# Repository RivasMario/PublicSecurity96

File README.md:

# PublicSecurity96
96% Mechanical Keyboard PCB Kicad Files

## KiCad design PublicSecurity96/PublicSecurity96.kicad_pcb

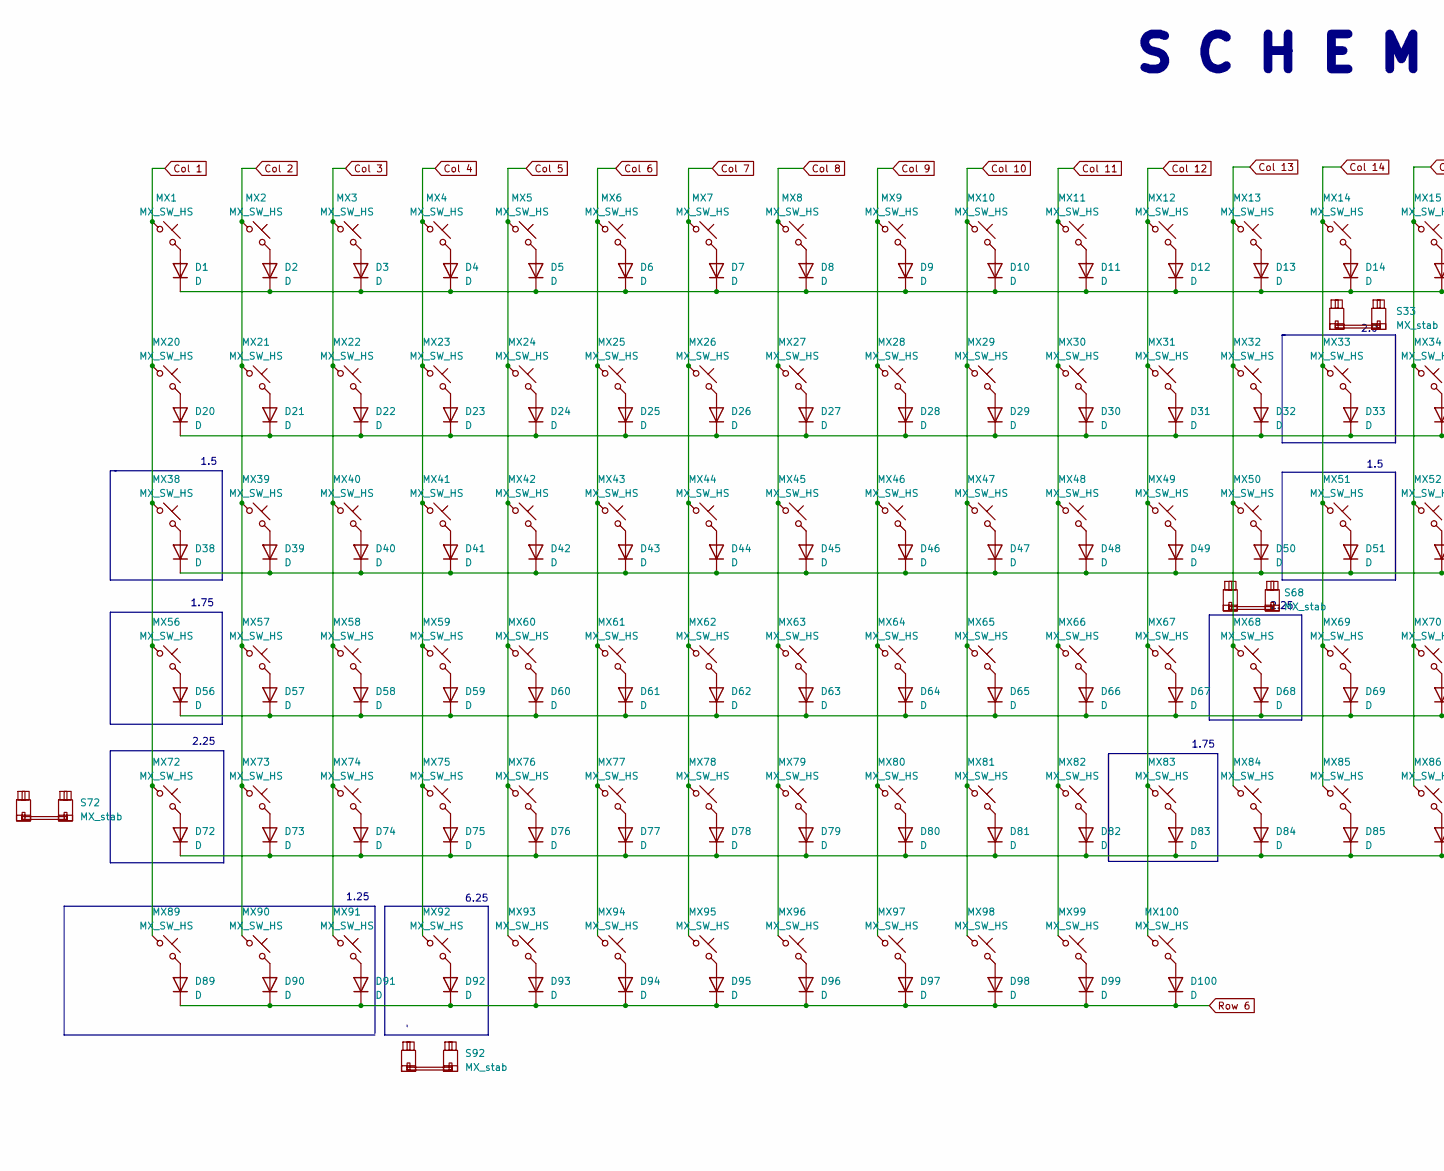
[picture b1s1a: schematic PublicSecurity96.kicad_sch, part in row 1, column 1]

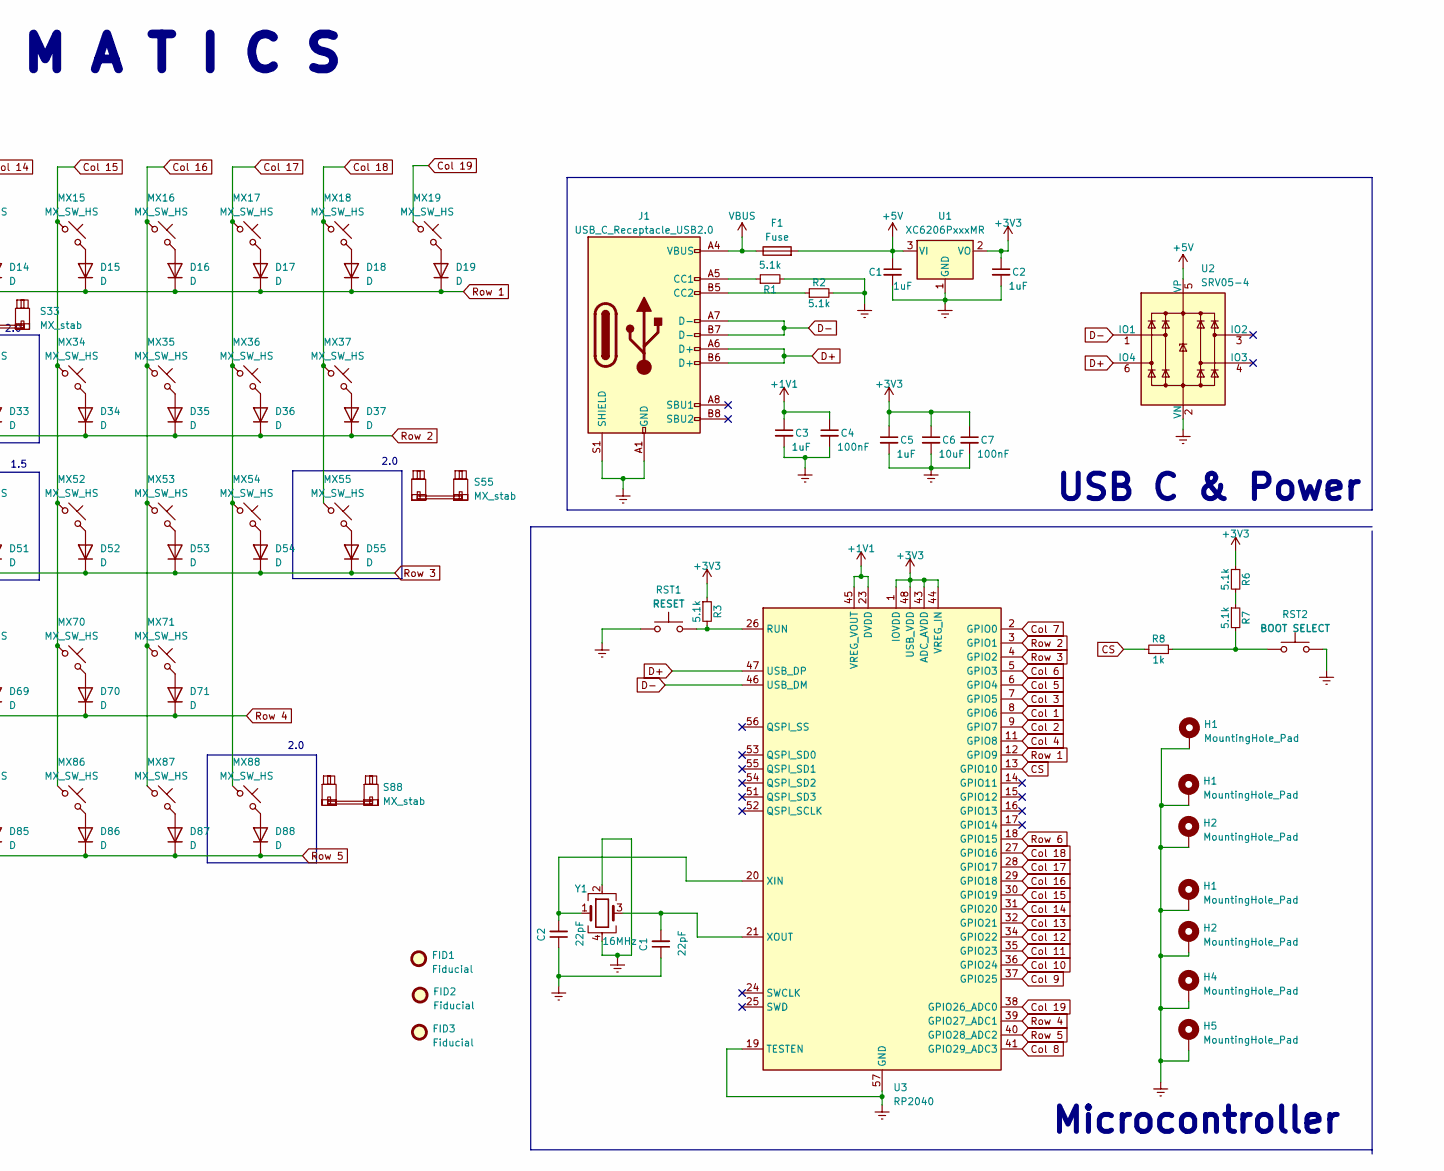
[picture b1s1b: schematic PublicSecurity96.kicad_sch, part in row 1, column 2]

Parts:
C1, C2: 1uF; C_0402_1005Metric_Pad0.74x0.62mm_HandSolder
C3, C5: 1uF; C_0402_1005Metric_Pad0.74x0.62mm_HandSolder; JLCPCB part# C52923
C4, C7: 100nF; C_0402_1005Metric_Pad0.74x0.62mm_HandSolder; JLCPCB part# C1525
C6: 10uF; C_0603_1608Metric; JLCPCB part# C19702
D1, D2, D3, D4, D5, D6, D7, D8, D9, D10, D11, D12, D13, D14, D15, D16, D17, D18, D19, D20, D21, D22, D23, D24, D25, D26, D27, D28, D29, D30, D31, D32, D33, D34, D35, D36, D37, D38, D39, D40, D41, D42, D43, D44, D45, D46, D47, D48, D49, D50, D51, D52, D53, D54, D55, D56, D57, D58, D59, D60, D61, D62, D63, D64, D65, D66, D67, D68, D69, D70, D71, D72, D73, D74, D75, D76, D77, D78, D79, D80, D81, D82, D83, D84, D85, D86, D87, D88, D89, D90, D91, D92, D93, D94, D95, D96, D97, D98, D99, D100: D; D_SOD-123
F1: Fuse; Fuse_0805_2012Metric; JLCPCB part# C3035895
FID1, FID2, FID3: Fiducial; Fiducial_1mm_Mask2mm
H1, H2, H4, H5: MountingHole_Pad; MountingHole_3.2mm_M3_DIN965_Pad
J1: USB_C_Receptacle_USB2.0; USB_C_Receptacle_HRO_TYPE-C-31-M-12; JLCPCB part# C165948
MX1, MX2, MX3, MX4, MX5, MX6, MX7, MX8, MX9, MX10, MX11, MX12, MX13, MX14, MX15, MX16, MX17, MX18, MX19, MX20, MX21, MX22, MX23, MX24, MX25, MX26, MX27, MX28, MX29, MX30, MX31, MX32, MX33, MX34, MX35, MX36, MX37, MX39, MX40, MX41, MX42, MX43, MX44, MX45, MX46, MX47, MX48, MX49, MX50, MX52, MX53, MX54, MX55, MX57, MX58, MX59, MX60, MX61, MX62, MX63, MX64, MX65, MX66, MX67, MX68, MX69, MX70, MX71, MX72, MX73, MX74, MX75, MX76, MX77, MX78, MX79, MX80, MX81, MX82, MX84, MX85, MX86, MX87, MX88, MX92, MX93, MX94, MX95, MX96, MX97, MX98, MX99, MX100: MX_SW_HS; SW_MX_HS_1u
MX38, MX51: MX_SW_HS; SW_MX_HS_1.5u
MX56, MX83: MX_SW_HS; SW_MX_HS_1.75u
MX89, MX90, MX91: MX_SW_HS; SW_MX_HS_1.25u
R1, R2, R3, R6, R7: 5.1k; R_0402_1005Metric_Pad0.72x0.64mm_HandSolder; JLCPCB part# C105872
R8: 1k; R_0402_1005Metric_Pad0.72x0.64mm_HandSolder; JLCPCB part# C2909306
RST1: RESET; SolderJumper-2_P1.3mm_Open_RoundedPad1.0x1.5mm
RST2: BOOT SELECT; SolderJumper-2_P1.3mm_Open_RoundedPad1.0x1.5mm
S33, S55, S88: MX_stab; STAB_MX_P_2u
S68, S72: MX_stab; STAB_MX_P_2.25u
S92: MX_stab; STAB_MX_P_6.25u
U1: XC6206PxxxMR; SOT-23-3; JLCPCB part# C47374
U2: SRV05-4; SOT-23-6-routable; JLCPCB part# C85364
U3: RP2040; QFN-56-1EP_7x7mm_P0.4mm_EP3.2x3.2mm; JLCPCB part# C2040
Y1: 16MHz; Crystal_SMD_3225-4Pin_3.2x2.5mm; JLCPCB part# C524715

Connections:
+1V1: C3.1, C4.1, U3.23 (DVDD), U3.45 (VREG_VOUT), U3.50 (DVDD)
Col 1: MX1.1, MX20.1, MX38.1, MX56.1, MX72.1, MX89.1, U3.8 (GPIO6)
Col 2: MX2.1, MX21.1, MX39.1, MX57.1, MX73.1, MX90.1, U3.9 (GPIO7)
Col 3: MX3.1, MX22.1, MX40.1, MX58.1, MX74.1, MX91.1, U3.7 (GPIO5)
Col 4: MX4.1, MX23.1, MX41.1, MX59.1, MX75.1, MX92.1, U3.11 (GPIO8)
Col 5: MX5.1, MX24.1, MX42.1, MX60.1, MX76.1, MX93.1, U3.6 (GPIO4)
Col 6: MX6.1, MX25.1, MX43.1, MX61.1, MX77.1, MX94.1, U3.5 (GPIO3)
Col 7: MX7.1, MX26.1, MX44.1, MX62.1, MX78.1, MX95.1, U3.2 (GPIO0)
Col 8: MX8.1, MX27.1, MX45.1, MX63.1, MX79.1, MX96.1, U3.41 (GPIO29_ADC3)
Col 9: MX9.1, MX28.1, MX46.1, MX64.1, MX80.1, MX97.1, U3.37 (GPIO25)
Col 10: MX10.1, MX29.1, MX47.1, MX65.1, MX81.1, MX98.1, U3.36 (GPIO24)
Col 11: MX11.1, MX30.1, MX48.1, MX66.1, MX82.1, MX99.1, U3.35 (GPIO23)
Col 12: MX12.1, MX31.1, MX49.1, MX67.1, MX83.1, MX100.1, U3.34 (GPIO22)
Col 13: MX13.1, MX32.1, MX50.1, MX68.1, MX84.1, U3.32 (GPIO21)
Col 14: MX14.1, MX33.1, MX51.1, MX69.1, MX85.1, U3.31 (GPIO20)
Col 15: MX15.1, MX34.1, MX52.1, MX70.1, MX86.1, U3.30 (GPIO19)
Col 16: MX16.1, MX35.1, MX53.1, MX71.1, MX87.1, U3.29 (GPIO18)
Col 17: MX17.1, MX36.1, MX54.1, MX88.1, U3.28 (GPIO17)
Col 18: MX18.1, MX37.1, MX55.1, U3.27 (GPIO16)
Col 19: MX19.1, U3.38 (GPIO26_ADC0)
D+: J1.A6 (D+), J1.B6 (D+), U2.6 (IO4), U3.47 (USB_DP)
D-: J1.A7 (D-), J1.B7 (D-), U2.1 (IO1), U3.46 (USB_DM)
unnamed: D1.2 (A), MX1.2
unnamed: D2.2 (A), MX2.2
unnamed: D3.2 (A), MX3.2
unnamed: D4.2 (A), MX4.2
unnamed: D5.2 (A), MX5.2
unnamed: D6.2 (A), MX6.2
unnamed: D7.2 (A), MX7.2
unnamed: D8.2 (A), MX8.2
unnamed: D9.2 (A), MX9.2
unnamed: D10.2 (A), MX10.2
unnamed: D11.2 (A), MX11.2
unnamed: D12.2 (A), MX12.2
unnamed: D13.2 (A), MX13.2
unnamed: D14.2 (A), MX14.2
unnamed: D15.2 (A), MX15.2
unnamed: D16.2 (A), MX16.2
unnamed: D17.2 (A), MX17.2
unnamed: D18.2 (A), MX18.2
unnamed: D19.2 (A), MX19.2
unnamed: D20.2 (A), MX20.2
unnamed: D21.2 (A), MX21.2
unnamed: D22.2 (A), MX22.2
unnamed: D23.2 (A), MX23.2
unnamed: D24.2 (A), MX24.2
unnamed: D25.2 (A), MX25.2
unnamed: D26.2 (A), MX26.2
unnamed: D27.2 (A), MX27.2
unnamed: D28.2 (A), MX28.2
unnamed: D29.2 (A), MX29.2
unnamed: D30.2 (A), MX30.2
unnamed: D31.2 (A), MX31.2
unnamed: D32.2 (A), MX32.2
unnamed: D33.2 (A), MX33.2
unnamed: D34.2 (A), MX34.2
unnamed: D35.2 (A), MX35.2
unnamed: D36.2 (A), MX36.2
unnamed: D37.2 (A), MX37.2
unnamed: D38.2 (A), MX38.2
unnamed: D39.2 (A), MX39.2
unnamed: D40.2 (A), MX40.2
unnamed: D41.2 (A), MX41.2
unnamed: D42.2 (A), MX42.2
unnamed: D43.2 (A), MX43.2
unnamed: D44.2 (A), MX44.2
unnamed: D45.2 (A), MX45.2
unnamed: D46.2 (A), MX46.2
unnamed: D47.2 (A), MX47.2
unnamed: D48.2 (A), MX48.2
unnamed: D49.2 (A), MX49.2
unnamed: D50.2 (A), MX50.2
unnamed: D51.2 (A), MX51.2
unnamed: D52.2 (A), MX52.2
unnamed: D53.2 (A), MX53.2
unnamed: D54.2 (A), MX54.2
unnamed: D55.2 (A), MX55.2
unnamed: D56.2 (A), MX56.2
unnamed: D57.2 (A), MX57.2
unnamed: D58.2 (A), MX58.2
unnamed: D59.2 (A), MX59.2
unnamed: D60.2 (A), MX60.2
unnamed: D61.2 (A), MX61.2
unnamed: D62.2 (A), MX62.2
unnamed: D63.2 (A), MX63.2
unnamed: D64.2 (A), MX64.2
unnamed: D65.2 (A), MX65.2
unnamed: D66.2 (A), MX66.2
unnamed: D67.2 (A), MX67.2
unnamed: D68.2 (A), MX68.2
unnamed: D69.2 (A), MX69.2
unnamed: D70.2 (A), MX70.2
unnamed: D71.2 (A), MX71.2
unnamed: D72.2 (A), MX72.2
unnamed: D73.2 (A), MX73.2
unnamed: D74.2 (A), MX74.2
unnamed: D75.2 (A), MX75.2
unnamed: D76.2 (A), MX76.2
unnamed: D77.2 (A), MX77.2
unnamed: D78.2 (A), MX78.2
unnamed: D79.2 (A), MX79.2
unnamed: D80.2 (A), MX80.2
unnamed: D81.2 (A), MX81.2
unnamed: D82.2 (A), MX82.2
unnamed: D83.2 (A), MX83.2
unnamed: D84.2 (A), MX84.2
unnamed: D85.2 (A), MX85.2
unnamed: D86.2 (A), MX86.2
unnamed: D87.2 (A), MX87.2
unnamed: D88.2 (A), MX88.2
unnamed: D89.2 (A), MX89.2
unnamed: D90.2 (A), MX90.2
unnamed: D91.2 (A), MX91.2
unnamed: D92.2 (A), MX92.2
unnamed: D93.2 (A), MX93.2
unnamed: D94.2 (A), MX94.2
unnamed: D95.2 (A), MX95.2
unnamed: D96.2 (A), MX96.2
unnamed: D97.2 (A), MX97.2
unnamed: D98.2 (A), MX98.2
unnamed: D99.2 (A), MX99.2
unnamed: D100.2 (A), MX100.2
unnamed: J1.A5 (CC1), R1.1
unnamed: J1.B5 (CC2), R2.1
unnamed: R3.2, RST1.2, U3.26 (RUN)
Row 1: D1.1 (K), D2.1 (K), D3.1 (K), D4.1 (K), D5.1 (K), D6.1 (K), D7.1 (K), D8.1 (K), D9.1 (K), D10.1 (K), D11.1 (K), D12.1 (K), D13.1 (K), D14.1 (K), D15.1 (K), D16.1 (K), D17.1 (K), D18.1 (K), D19.1 (K), U3.12 (GPIO9)
Row 2: D20.1 (K), D21.1 (K), D22.1 (K), D23.1 (K), D24.1 (K), D25.1 (K), D26.1 (K), D27.1 (K), D28.1 (K), D29.1 (K), D30.1 (K), D31.1 (K), D32.1 (K), D33.1 (K), D34.1 (K), D35.1 (K), D36.1 (K), D37.1 (K), U3.3 (GPIO1)
Row 3: D38.1 (K), D39.1 (K), D40.1 (K), D41.1 (K), D42.1 (K), D43.1 (K), D44.1 (K), D45.1 (K), D46.1 (K), D47.1 (K), D48.1 (K), D49.1 (K), D50.1 (K), D51.1 (K), D52.1 (K), D53.1 (K), D54.1 (K), D55.1 (K), U3.4 (GPIO2)
Row 4: D56.1 (K), D57.1 (K), D58.1 (K), D59.1 (K), D60.1 (K), D61.1 (K), D62.1 (K), D63.1 (K), D64.1 (K), D65.1 (K), D66.1 (K), D67.1 (K), D68.1 (K), D69.1 (K), D70.1 (K), D71.1 (K), U3.39 (GPIO27_ADC1)
Row 5: D72.1 (K), D73.1 (K), D74.1 (K), D75.1 (K), D76.1 (K), D77.1 (K), D78.1 (K), D79.1 (K), D80.1 (K), D81.1 (K), D82.1 (K), D83.1 (K), D84.1 (K), D85.1 (K), D86.1 (K), D87.1 (K), D88.1 (K), U3.40 (GPIO28_ADC2)
Row 6: D89.1 (K), D90.1 (K), D91.1 (K), D92.1 (K), D93.1 (K), D94.1 (K), D95.1 (K), D96.1 (K), D97.1 (K), D98.1 (K), D99.1 (K), D100.1 (K), U3.18 (GPIO15)
VBUS: F1.1, J1.A4 (VBUS), J1.A9 (VBUS), J1.B4 (VBUS), J1.B9 (VBUS)

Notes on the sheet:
1.5
2.25
1.75
2.0
6.25
Microcontroller
1.25
S C H E M A T I C S
USB C & Power

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
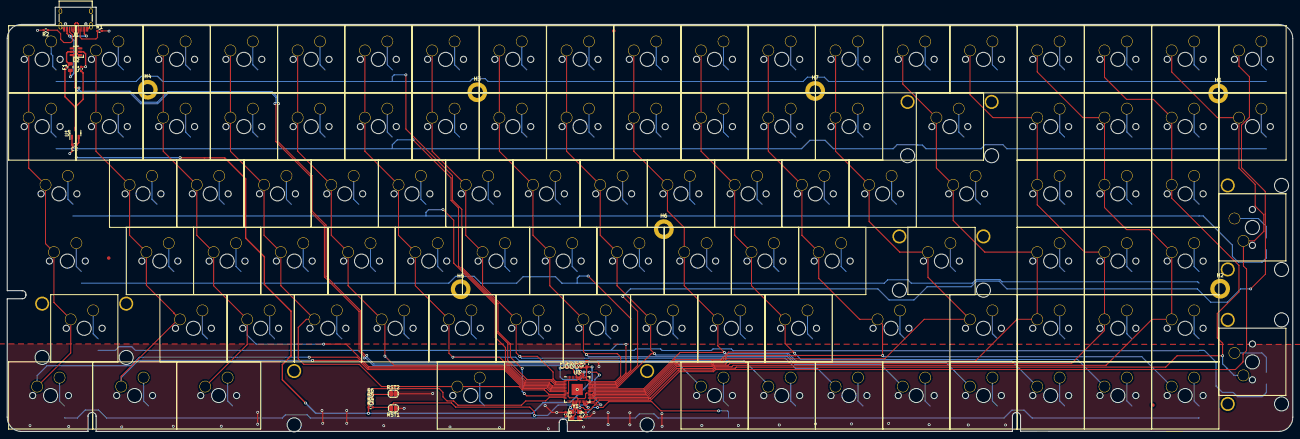
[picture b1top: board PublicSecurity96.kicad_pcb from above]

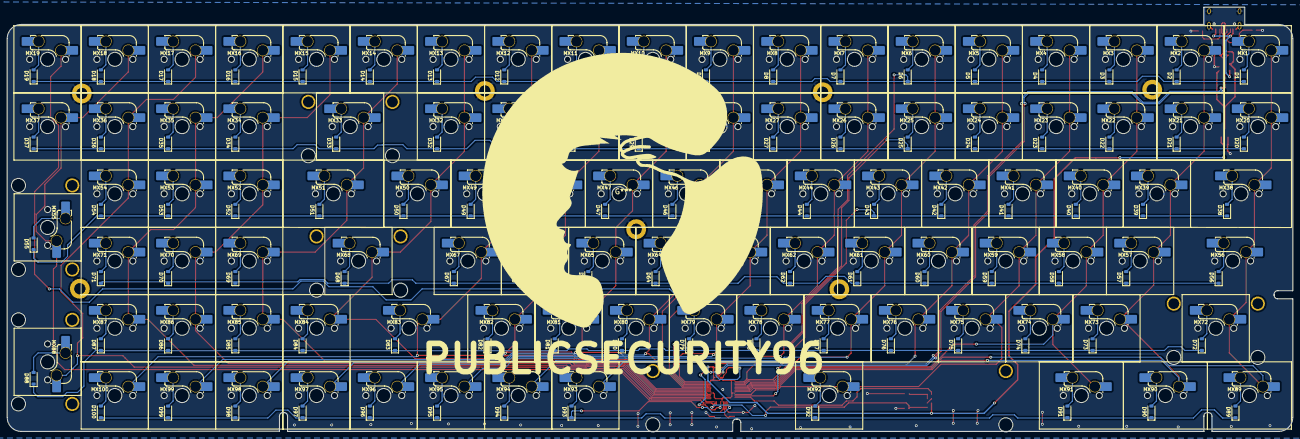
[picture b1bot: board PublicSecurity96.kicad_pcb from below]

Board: 2 copper layers, 364.2 x 120.2 mm, 239 parts (200 on the bottom side), 140 nets.

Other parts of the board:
C8, C9: 22pF; C_0402_1005Metric_Pad0.74x0.62mm_HandSolder
H3, H6, H7: MountingHole_Pad; MountingHole_3.2mm_M3_DIN965_Pad
R4, R5: 5.1k; R_0402_1005Metric_Pad0.72x0.64mm_HandSolder

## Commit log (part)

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2024-06-25 Initial Commit
    Initial Commit
2026-04-29 kicad: swap U1 XC6206 -> AMS1117-3.3 (SOT-223 + C6186)
2026-04-29 wip: place R20 27R on D+ (right-pad snap to pin 47 pending)
2026-04-29 docs: TOMORROW.md - resume notes for R20 snap + remaining work
